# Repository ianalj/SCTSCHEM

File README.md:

# SCHEMATICS FOR MY SPECIFIC PROJECT

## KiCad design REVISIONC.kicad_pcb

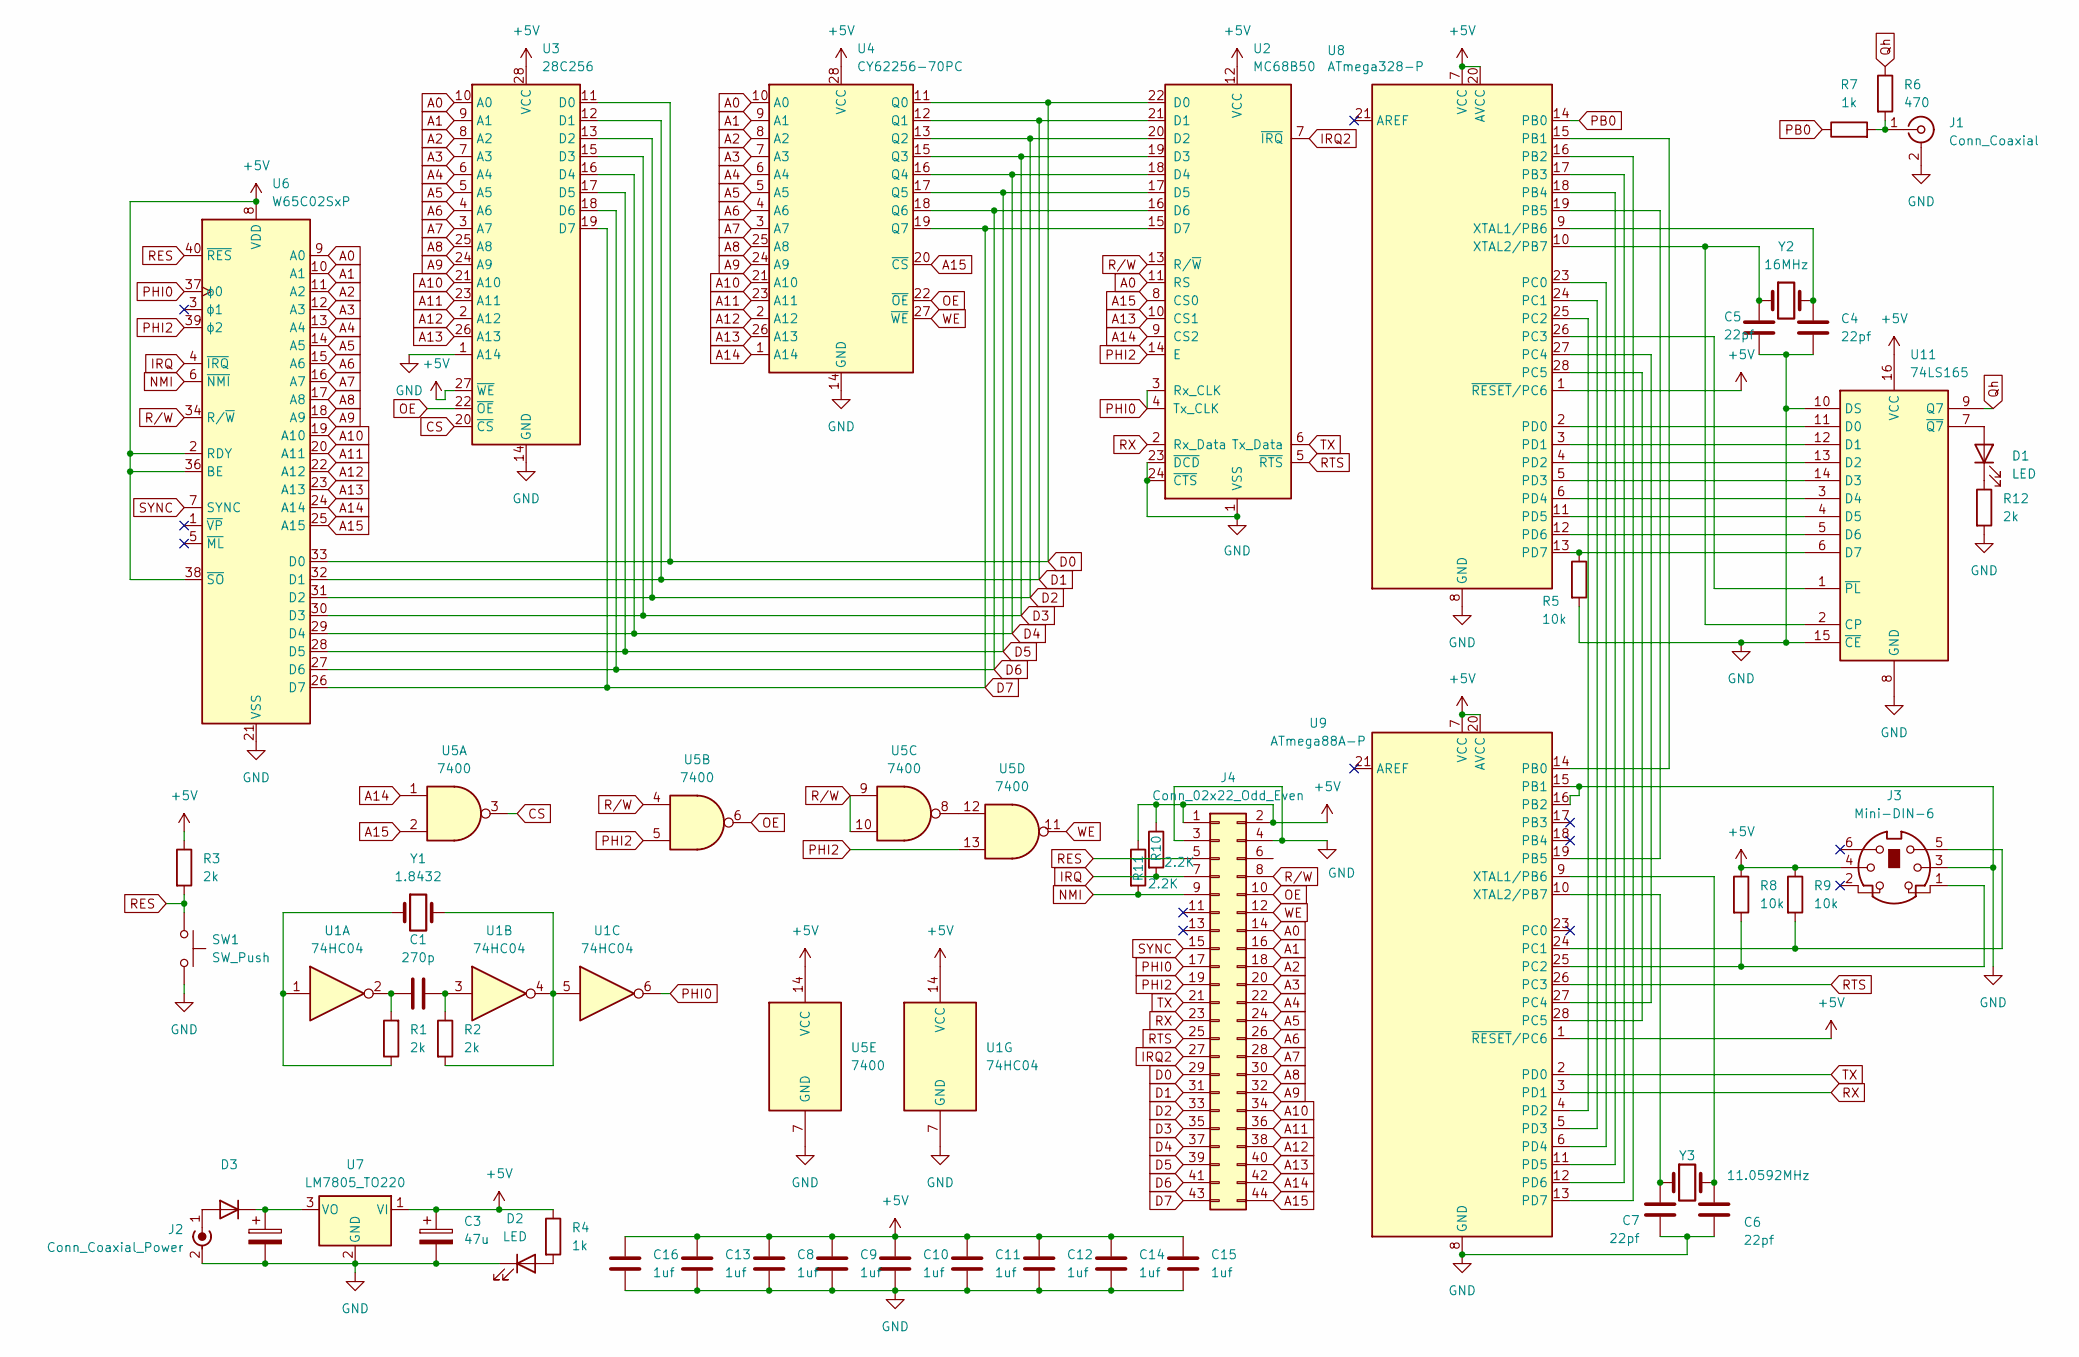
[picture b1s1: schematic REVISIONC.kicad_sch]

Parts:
C1: 270p; C_Disc_D5.0mm_W2.5mm_P5.00mm
C2: 470uf; C_Disc_D5.0mm_W2.5mm_P5.00mm
C3: 47u; C_Disc_D5.0mm_W2.5mm_P5.00mm
C4, C5, C6, C7: 22pf; C_Disc_D5.0mm_W2.5mm_P5.00mm
C8, C9, C10, C11, C12, C13, C14, C15, C16: 1uf; C_Disc_D5.0mm_W2.5mm_P5.00mm
D1: LED; LED_D5.0mm
D2: LED; LED_D5.0mm_Horizontal_O1.27mm_Z3.0mm
D3: 1N4007; D_DO-41_SOD81_P10.16mm_Horizontal
J1: Conn_Coaxial; CUI_RCJ-014
J2: Conn_Coaxial_Power; MPD_EJ508A
J3: Mini-DIN-6; KMDTX_HT_6S_BSC
J4: Conn_02x22_Odd_Even; Untitled
R1, R2, R3, R12: 2k; R_Axial_DIN0207_L6.3mm_D2.5mm_P7.62mm_Horizontal
R4, R7: 1k; R_Axial_DIN0207_L6.3mm_D2.5mm_P7.62mm_Horizontal
R5, R8, R9: 10k; R_Axial_DIN0207_L6.3mm_D2.5mm_P7.62mm_Horizontal
R6: 470; R_Axial_DIN0207_L6.3mm_D2.5mm_P7.62mm_Horizontal
R10, R11: 2.2K; R_Axial_DIN0207_L6.3mm_D2.5mm_P7.62mm_Horizontal
SW1: SW_Push; SW_PUSH_6mm
U1: 74HC04; DIP-14_W7.62mm_LongPads
U2: MC68B50; DIP-24_W15.24mm_LongPads
U3: 28C256; DIP-28_W15.24mm_LongPads
U4: CY62256-70PC; DIP-28_W15.24mm_LongPads
U5: 7400; DIP-14_W7.62mm_LongPads
U6: W65C02SxP; DIP-40_W15.24mm_LongPads
U7: LM7805_TO220; TO-220-3_Vertical
U8: ATmega328-P; DIP-28_W7.62mm_LongPads
U9: ATmega88A-P; DIP-28_W7.62mm_LongPads
U11: 74LS165; DIP-16_W7.62mm_LongPads
Y1: 1.8432; Crystal_HC49-U_Vertical
Y2: 16MHz; Crystal_HC49-4H_Vertical
Y3: 11.0592MHz; Crystal_HC49-4H_Vertical

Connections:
+5V: C3.1, C8.1, C9.1, C10.1, C11.1, C12.1, C13.1, C14.1, C15.1, C16.1, J3.4, J4.1, J4.2, R3.1, R4.1, R8.1, R9.1, R10.1, R11.1, U1.14 (VCC), U2.12 (VCC), U3.27 (~WE), U3.28 (VCC), U4.28 (VCC), U5.14 (VCC), U6.2 (RDY), U6.8 (VDD), U6.36 (BE), U6.38 (~SO), U7.1 (VI), U8.1 (~RESET/PC6), U8.7 (VCC), U8.20 (AVCC), U9.1 (~RESET/PC6), U9.7 (VCC), U9.20 (AVCC), U11.16 (VCC); also elsewhere on the board
A0: J4.14, U2.11 (RS), U3.10 (A0), U4.10 (A0), U6.9 (A0); also elsewhere on the board
A1: J4.16, U3.9 (A1), U4.9 (A1), U6.10 (A1); also elsewhere on the board
A2: J4.18, U3.8 (A2), U4.8 (A2), U6.11 (A2); also elsewhere on the board
A3: J4.20, U3.7 (A3), U4.7 (A3), U6.12 (A3); also elsewhere on the board
A4: J4.22, U3.6 (A4), U4.6 (A4), U6.13 (A4); also elsewhere on the board
A5: J4.24, U3.5 (A5), U4.5 (A5), U6.14 (A5); also elsewhere on the board
A6: J4.26, U3.4 (A6), U4.4 (A6), U6.15 (A6); also elsewhere on the board
A7: J4.28, U3.3 (A7), U4.3 (A7), U6.16 (A7); also elsewhere on the board
A8: J4.30, U3.25 (A8), U4.25 (A8), U6.17 (A8); also elsewhere on the board
A9: J4.32, U3.24 (A9), U4.24 (A9), U6.18 (A9); also elsewhere on the board
A10: J4.34, U3.21 (A10), U4.21 (A10), U6.19 (A10); also elsewhere on the board
A11: J4.36, U3.23 (A11), U4.23 (A11), U6.20 (A11); also elsewhere on the board
A12: J4.38, U3.2 (A12), U4.2 (A12), U6.22 (A12); also elsewhere on the board
A13: J4.40, U2.10 (CS1), U3.26 (A13), U4.26 (A13), U6.23 (A13); also elsewhere on the board
A14: J4.42, U2.9 (CS2), U4.1 (A14), U5.1, U6.24 (A14); also elsewhere on the board
A15: J4.44, U2.8 (CS0), U4.20 (~CS), U5.2, U6.25 (A15); also elsewhere on the board
CS: U3.20 (~CS), U5.3
D0: J4.29, U2.22 (D0), U3.11 (D0), U4.11 (Q0), U6.33 (D0); also elsewhere on the board
D1: J4.31, U2.21 (D1), U3.12 (D1), U4.12 (Q1), U6.32 (D1); also elsewhere on the board
D2: J4.33, U2.20 (D2), U3.13 (D2), U4.13 (Q2), U6.31 (D2); also elsewhere on the board
D3: J4.35, U2.19 (D3), U3.15 (D3), U4.15 (Q3), U6.30 (D3); also elsewhere on the board
D4: J4.37, U2.18 (D4), U3.16 (D4), U4.16 (Q4), U6.29 (D4); also elsewhere on the board
D5: J4.39, U2.17 (D5), U3.17 (D5), U4.17 (Q5), U6.28 (D5); also elsewhere on the board
D6: J4.41, U2.16 (D6), U3.18 (D6), U4.18 (Q6), U6.27 (D6); also elsewhere on the board
D7: J4.43, U2.15 (D7), U3.19 (D7), U4.19 (Q7), U6.26 (D7); also elsewhere on the board
GND: C2.2, C3.2, C4.2, C5.2, C6.2, C7.2, C8.2, C9.2, C10.2, C11.2, C12.2, C13.2, C14.2, C15.2, C16.2, D2.1 (K), J1.2 (Ext), J2.2 (Ext), J2.3, J3.3, J4.3, J4.4, R5.2, R12.2, SW1.2, U1.7 (GND), U2.1 (VSS), U2.23 (~DCD), U2.24 (~CTS), U3.1 (A14), U3.14 (GND), U4.14 (GND), U5.7 (GND), U6.21 (VSS), U7.2 (GND), U8.8 (GND), U8.22 (GND), U9.8 (GND), U9.15 (PB1), U9.16 (PB2), U9.22 (GND), U11.8 (GND), U11.10 (DS), U11.15 (~CE); also elsewhere on the board
IRQ: J4.7, R10.2, U6.4 (~IRQ); also elsewhere on the board
IRQ2: J4.27, U2.7 (~IRQ); also elsewhere on the board
NMI: J4.9, R11.2, U6.6 (~NMI); also elsewhere on the board
unnamed: C1.1, R2.1, U1.3
unnamed: C1.2, R1.2, U1.2
unnamed: D1.2 (A), U11.7 (~Q7)
unnamed: D1.1 (K), R12.1
unnamed: D2.2 (A), R4.2
unnamed: D3.2 (A), J2.1 (In)
unnamed: C2.1, D3.1 (K), U7.3 (VO)
unnamed: J1.1 (In), R6.2, R7.2
unnamed: R1.1, U1.1, Y1.1
unnamed: R2.2, U1.4, U1.5, Y1.2
unnamed: U5.8, U5.12
unnamed: U8.15 (PB1), U9.14 (PB0)
unnamed: U8.16 (PB2), U9.13 (PD7)
unnamed: U8.17 (PB3), U9.12 (PD6)
unnamed: U8.18 (PB4), U9.11 (PD5)
unnamed: U8.19 (PB5), U9.19 (PB5)
unnamed: U8.23 (PC0), U9.6 (PD4)
unnamed: U8.24 (PC1), U9.5 (PD3)
unnamed: U8.25 (PC2), U9.4 (PD2)
unnamed: U8.27 (PC4), U9.27 (PC4)
unnamed: U8.28 (PC5), U9.28 (PC5)
unnamed: C4.1, U8.9 (XTAL1/PB6), Y2.2
unnamed: J3.5, R9.2, U9.24 (PC1)
unnamed: J3.1, R8.2, U9.25 (PC2)
unnamed: C6.1, U9.9 (XTAL1/PB6), Y3.2
unnamed: C7.1, U9.10 (XTAL2/PB7), Y3.1
unnamed: C5.1, U8.10 (XTAL2/PB7), U11.2 (CP), Y2.1
unnamed: U8.2 (PD0), U11.11 (D0)
unnamed: U8.3 (PD1), U11.12 (D1)
unnamed: U8.4 (PD2), U11.13 (D2)
unnamed: U8.5 (PD3), U11.14 (D3)
unnamed: U8.6 (PD4), U11.3 (D4)
unnamed: U8.11 (PD5), U11.4 (D5)
unnamed: U8.12 (PD6), U11.5 (D6)
unnamed: R5.1, U8.13 (PD7), U11.6 (D7)
unnamed: U8.26 (PC3), U11.1 (~PL)
OE: J4.10, U3.22 (~OE), U4.22 (~OE), U5.6; also elsewhere on the board
PB0: R7.1, U8.14 (PB0)
PHI0: J4.17, U1.6, U2.3 (Rx_CLK), U2.4 (Tx_CLK), U6.37 (ϕ0); also elsewhere on the board
PHI2: J4.19, U2.14 (E), U5.5, U5.13, U6.39 (ϕ2); also elsewhere on the board
Qh: R6.1, U11.9 (Q7)
RES: J4.5, R3.2, SW1.1, U6.40 (~RES); also elsewhere on the board
RTS: J4.25, U2.5 (~RTS), U9.26 (PC3); also elsewhere on the board
R/W: J4.8, U2.13 (R/~W), U5.4, U5.9, U5.10, U6.34 (R/~W); also elsewhere on the board
SYNC: J4.15, U6.7 (SYNC); also elsewhere on the board
WE: J4.12, U4.27 (~WE), U5.11; also elsewhere on the board

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
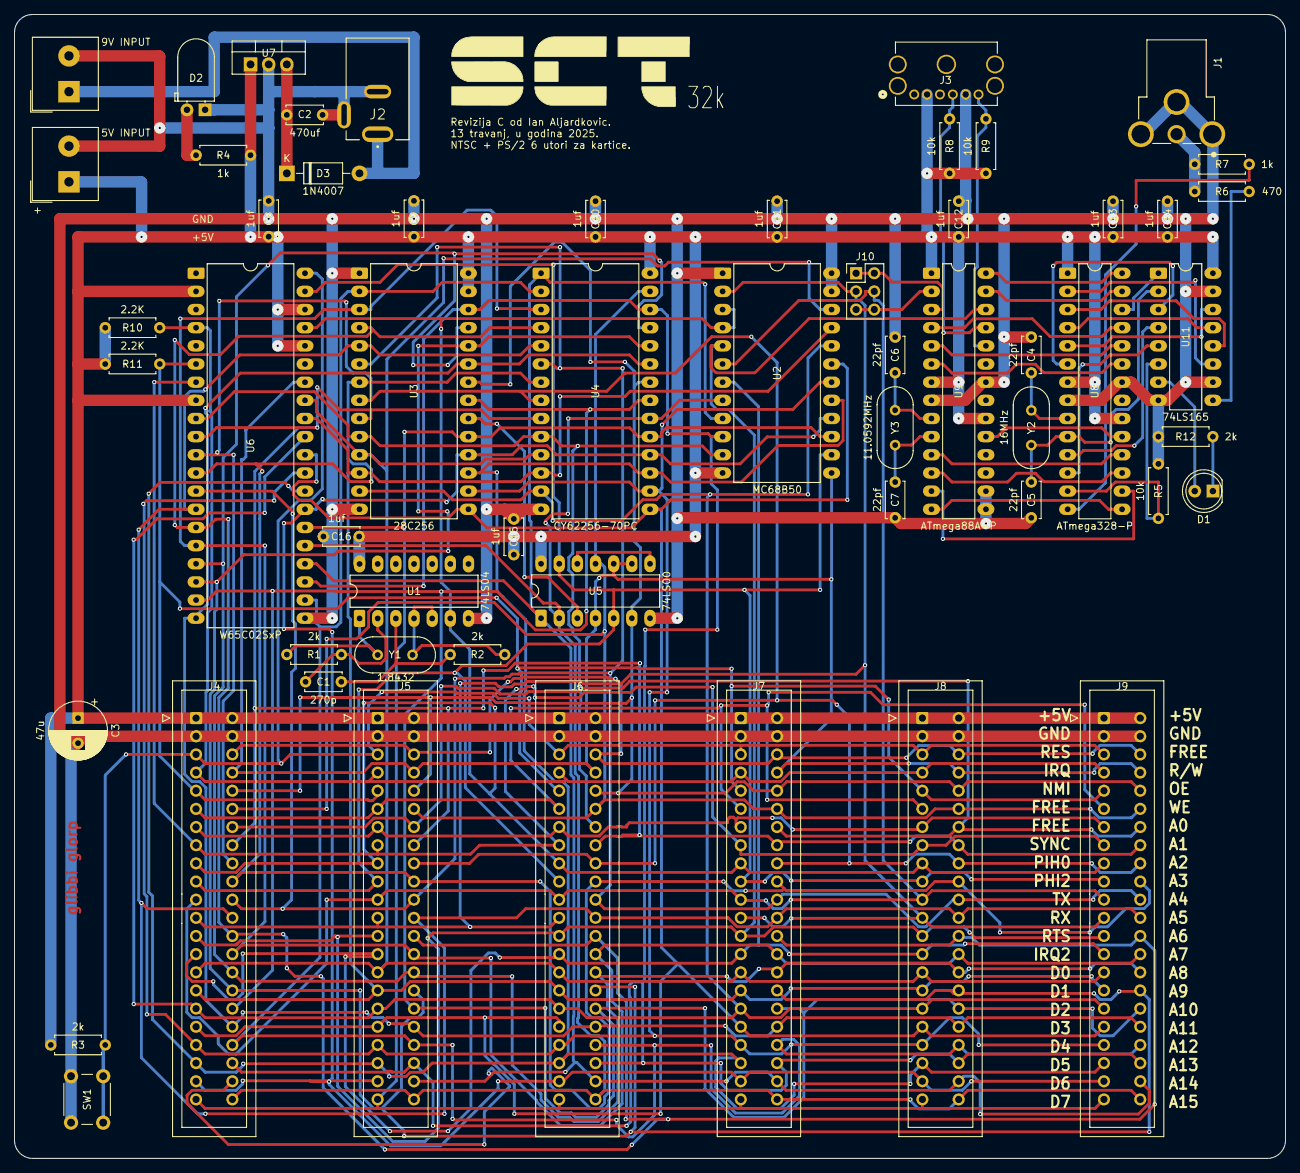
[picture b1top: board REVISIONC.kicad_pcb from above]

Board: 2 copper layers, 177.8 x 160.0 mm, 55 parts (0 on the bottom side), 80 nets.

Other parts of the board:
J5, J6, J7, J8, J9: Conn_02x22_Odd_Even; Card_Slot_2x22_P2.54mm_Vertical
J10: Conn_02x03_Odd_Even; PinHeader_2x03_P2.54mm_Vertical

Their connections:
+5V: J5.1, J5.2, J6.1, J6.2, J7.1, J7.2, J8.1, J8.2, J9.1, J9.2; also elsewhere on the board
A0: J5.14, J6.14, J7.14, J8.14, J9.14; also elsewhere on the board
A1: J5.16, J6.16, J7.16, J8.16, J9.16; also elsewhere on the board
A2: J5.18, J6.18, J7.18, J8.18, J9.18; also elsewhere on the board
A3: J5.20, J6.20, J7.20, J8.20, J9.20; also elsewhere on the board
A4: J5.22, J6.22, J7.22, J8.22, J9.22; also elsewhere on the board
A5: J5.24, J6.24, J7.24, J8.24, J9.24; also elsewhere on the board
A6: J5.26, J6.26, J7.26, J8.26, J9.26; also elsewhere on the board
A7: J5.28, J6.28, J7.28, J8.28, J9.28; also elsewhere on the board
A8: J5.30, J6.30, J7.30, J8.30, J9.30; also elsewhere on the board
A9: J5.32, J6.32, J7.32, J8.32, J9.32; also elsewhere on the board
A10: J5.34, J6.34, J7.34, J8.34, J9.34; also elsewhere on the board
A11: J5.36, J6.36, J7.36, J8.36, J9.36; also elsewhere on the board
A12: J5.38, J6.38, J7.38, J8.38, J9.38; also elsewhere on the board
A13: J5.40, J6.40, J7.40, J8.40, J9.40; also elsewhere on the board
A14: J5.42, J6.42, J7.42, J8.42, J9.42; also elsewhere on the board
A15: J5.44, J6.44, J7.44, J8.44, J9.44; also elsewhere on the board
D0: J5.29, J6.29, J7.29, J8.29, J9.29; also elsewhere on the board
D1: J5.31, J6.31, J7.31, J8.31, J9.31; also elsewhere on the board
D2: J5.33, J6.33, J7.33, J8.33, J9.33; also elsewhere on the board
D3: J5.35, J6.35, J7.35, J8.35, J9.35; also elsewhere on the board
D4: J5.37, J6.37, J7.37, J8.37, J9.37; also elsewhere on the board
D5: J5.39, J6.39, J7.39, J8.39, J9.39; also elsewhere on the board
D6: J5.41, J6.41, J7.41, J8.41, J9.41; also elsewhere on the board
D7: J5.43, J6.43, J7.43, J8.43, J9.43; also elsewhere on the board
GND: J5.3, J5.4, J6.3, J6.4, J7.3, J7.4, J8.3, J8.4, J9.3, J9.4; also elsewhere on the board
IRQ: J5.7, J6.7, J7.7, J8.7, J9.7; also elsewhere on the board
IRQ2: J5.27, J6.27, J7.27, J8.27, J9.27; also elsewhere on the board
NMI: J5.9, J6.9, J7.9, J8.9, J9.9; also elsewhere on the board
OE: J5.10, J6.10, J7.10, J8.10, J9.10; also elsewhere on the board
PHI0: J5.17, J6.17, J7.17, J8.17, J9.17; also elsewhere on the board
PHI2: J5.19, J6.19, J7.19, J8.19, J9.19; also elsewhere on the board
RES: J5.5, J6.5, J7.5, J8.5, J9.5; also elsewhere on the board
RTS: J5.25, J6.25, J7.25, J8.25, J9.25; also elsewhere on the board
R/W: J5.8, J6.8, J7.8, J8.8, J9.8; also elsewhere on the board
SYNC: J5.15, J6.15, J7.15, J8.15, J9.15; also elsewhere on the board
WE: J5.12, J6.12, J7.12, J8.12, J9.12; also elsewhere on the board

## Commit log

2025-05-20 Rename image.png to schematic.png
